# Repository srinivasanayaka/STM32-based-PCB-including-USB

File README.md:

# STM32-based-PCB-including-USB
Complete PCB design process going through the schematic, layout, routing of STM32 based USB pcb with 2 layer using Ki cad software

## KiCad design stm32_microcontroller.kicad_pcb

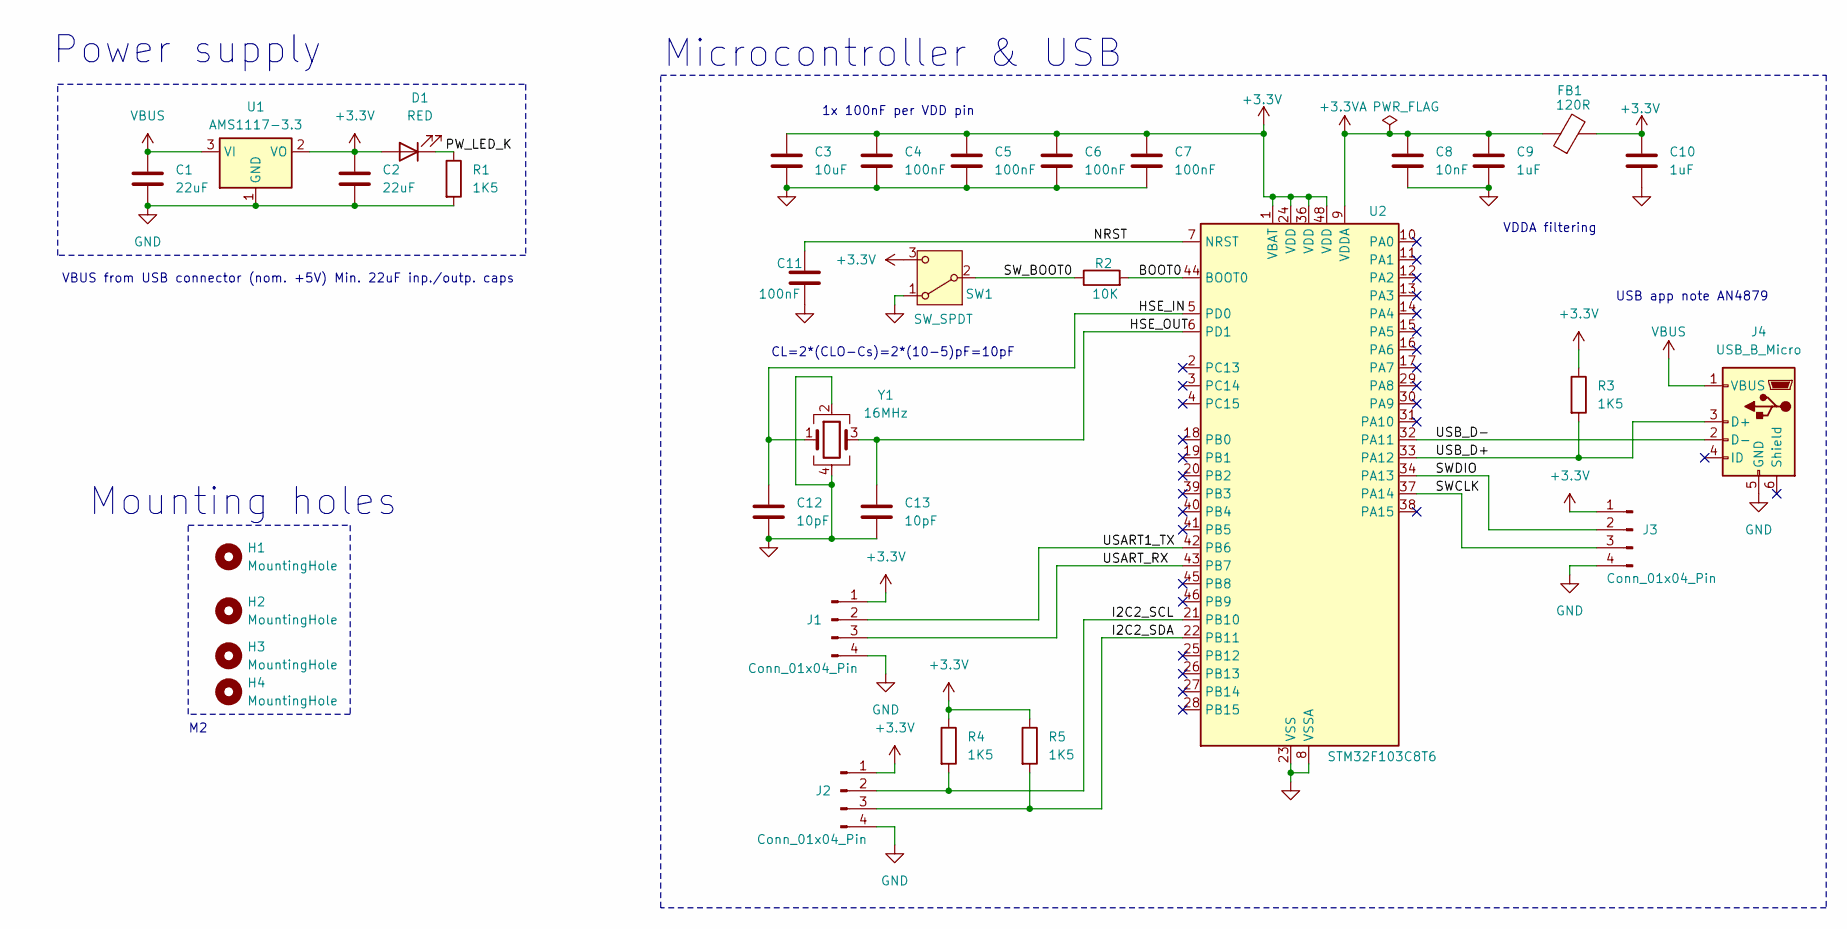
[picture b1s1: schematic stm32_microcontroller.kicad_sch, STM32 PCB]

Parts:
C1, C2: 22uF; C_0805_2012Metric
C3: 10uF; C_0603_1608Metric
C4, C5, C6, C7, C11: 100nF; C_0402_1005Metric
C8: 10nF; C_0402_1005Metric
C9, C10: 1uF; C_0402_1005Metric
C12, C13: 10pF; C_0402_1005Metric
D1: RED; LED_0603_1608Metric
FB1: 120R; L_0603_1608Metric
H1, H2, H3, H4: MountingHole; MountingHole_2.2mm_M2
J1, J2, J3: Conn_01x04_Pin; PinHeader_1x04_P2.54mm_Vertical
J4: USB_B_Micro; USB_Micro-B_Wuerth_629105150521
R1, R3, R4, R5: 1K5; R_0402_1005Metric
R2: 10K; R_0402_1005Metric
SW1: SW_SPDT; SW_SPDT_PCM12
U1: AMS1117-3.3; SOT-223-3_TabPin2
U2: STM32F103C8T6; LQFP-48_7x7mm_P0.5mm
Y1: 16MHz; Crystal_SMD_3225-4Pin_3.2x2.5mm

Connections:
+3.3V: C2.1, C3.1, C4.1, C5.1, C6.1, C7.1, C10.1, D1.2 (A), FB1.2, J1.1, J2.1, J3.1, R3.1, R4.1, R5.1, SW1.3 (C), U1.2 (VO), U2.1 (VBAT), U2.24 (VDD), U2.36 (VDD), U2.48 (VDD)
+3.3VA: C8.1, C9.1, FB1.1, U2.9 (VDDA)
/BOOT0: R2.2, U2.44 (BOOT0)
/HSE_IN: C12.1, U2.5 (PD0), Y1.1
/HSE_OUT: C13.1, U2.6 (PD1), Y1.3
/I2C2_SCL: J2.2, R4.2, U2.21 (PB10)
/I2C2_SDA: J2.3, R5.2, U2.22 (PB11)
/NRST: C11.1, U2.7 (NRST)
/PW_LED_K: D1.1 (K), R1.1
/SWCLK: J3.3, U2.37 (PA14)
/SWDIO: J3.2, U2.34 (PA13)
/SW_BOOT0: R2.1, SW1.2 (B)
/USART1_TX: J1.2, U2.42 (PB6)
/USART_RX: J1.3, U2.43 (PB7)
/USB_D+: J4.3 (D+), R3.2, U2.33 (PA12)
/USB_D-: J4.2 (D-), U2.32 (PA11)
GND: C1.2, C2.2, C3.2, C4.2, C5.2, C6.2, C7.2, C8.2, C9.2, C10.2, C11.2, C12.2, C13.2, J1.4, J2.4, J3.4, J4.5 (GND), R1.2, SW1.1 (A), U1.1 (GND), U2.8 (VSSA), U2.23 (VSS), U2.35 (VSS), U2.47 (VSS), Y1.2, Y1.4
VBUS: C1.1, J4.1 (VBUS), U1.3 (VI)

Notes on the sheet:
1x 100nF per VDD pin
VBUS from USB connector (nom. +5V) Min. 22uF inp./outp. caps
CL=2*(CLO-Cs)=2*(10-5)pF=10pF
VDDA filtering
Power supply
Microcontroller & USB
Mounting holes
USB app note AN4879

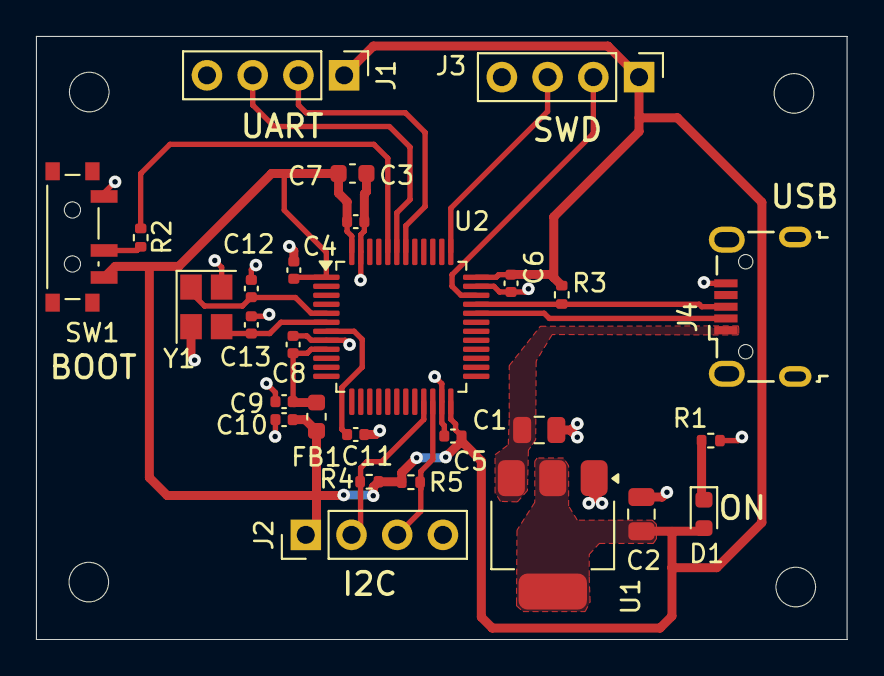
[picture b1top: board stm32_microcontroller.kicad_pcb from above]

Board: 2 copper layers, 45.0 x 33.5 mm, 32 parts (0 on the bottom side), 18 nets.
